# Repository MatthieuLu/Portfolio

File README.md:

# Portfolio
 
Hello, and welcome to my Portfolio!

My name is Matt, and I'm an Aerospace Engineering Student in the UCI Class of 2022.

I'm currently working towards getting my foot in the door to the Aerospace sector, hopefully as a Systems Engineer.

Here is a culmination of all of my past documented works, so feel free to browse and download what you would like.

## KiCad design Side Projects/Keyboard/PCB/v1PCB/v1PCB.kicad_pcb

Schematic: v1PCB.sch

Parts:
D_0, D_1, D_2, D_3, D_4, D_5, D_6, D_7, D_8, D_9, D_10, D_11, D_12, D_13, D_14, D_15, D_16, D_17, D_18, D_19, D_20, D_21, D_22, D_23, D_24, D_25, D_26, D_27, D_28, D_29, D_30, D_31, D_32, D_33, D_34, D_35, D_36, D_37, D_38, D_39, D_40, D_41, D_42, D_43, D_44, D_45, D_46, D_47, D_48, D_49, D_50, D_51, D_52, D_53, D_54, D_55, D_56, D_57, D_58, D_59, D_60, D_61, D_62, D_63, D_64, D_65, D_66, D_67, D_68, D_69, D_70, D_71, D_72, D_73, D_74, D_75, D_76, D_77, D_78, D_79, D_80, D_81, D_82, D_83, D_84, D_85, D_86, D_87, D_88, D_89, D_90, D_91, D_92, D_93, D_94, D_95, D_96, D_97, D_98, D_99, D_100: D; D_SOD-123
K_0, K_1, K_2, K_3, K_4, K_5, K_6, K_7, K_8, K_9, K_10, K_11, K_12, K_13, K_14, K_15, K_16, K_17, K_18, K_19, K_20, K_21, K_22, K_23, K_24, K_25, K_26, K_27, K_28, K_29, K_30, K_31, K_33, K_34, K_35, K_36, K_38, K_39, K_40, K_41, K_42, K_43, K_44, K_45, K_46, K_47, K_48, K_49, K_51, K_52, K_53, K_54, K_56, K_57, K_58, K_59, K_60, K_61, K_62, K_63, K_64, K_65, K_66, K_68, K_69, K_70, K_72, K_73, K_74, K_75, K_76, K_77, K_78, K_79, K_80, K_81, K_83, K_84, K_85, K_86, K_87, K_96, K_97, K_98, K_99, K_100: KEYSW; MX-1U-NoLED
K_32: KEYSW; MX-2U-NoLED
K_37, K_50: KEYSW; MX-1.5U-NoLED
K_55, K_82: KEYSW; MX-1.75U-NoLED
K_67, K_71, K_91: KEYSW; MX-2.25U-NoLED
K_88, K_89, K_90, K_92, K_94, K_95: KEYSW; MX-1.25U-NoLED
K_93: KEYSW; MX-2.75U-NoLED

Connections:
unnamed: D_0.2 (A), K_0.2
unnamed: D_1.2 (A), K_1.2
unnamed: D_2.2 (A), K_2.2
unnamed: D_3.2 (A), K_3.2
unnamed: D_4.2 (A), K_4.2
unnamed: D_5.2 (A), K_5.2
unnamed: D_6.2 (A), K_6.2
unnamed: D_7.2 (A), K_7.2
unnamed: D_8.2 (A), K_8.2
unnamed: D_9.2 (A), K_9.2
unnamed: D_10.2 (A), K_10.2
unnamed: D_11.2 (A), K_11.2
unnamed: D_12.2 (A), K_12.2
unnamed: D_13.2 (A), K_13.2
unnamed: D_14.2 (A), K_14.2
unnamed: D_15.2 (A), K_15.2
unnamed: D_16.2 (A), K_16.2
unnamed: D_17.2 (A), K_17.2
unnamed: D_18.2 (A), K_18.2
unnamed: D_19.2 (A), K_19.2
unnamed: D_20.2 (A), K_20.2
unnamed: D_21.2 (A), K_21.2
unnamed: D_22.2 (A), K_22.2
unnamed: D_23.2 (A), K_23.2
unnamed: D_24.2 (A), K_24.2
unnamed: D_25.2 (A), K_25.2
unnamed: D_26.2 (A), K_26.2
unnamed: D_27.2 (A), K_27.2
unnamed: D_28.2 (A), K_28.2
unnamed: D_29.2 (A), K_29.2
unnamed: D_30.2 (A), K_30.2
unnamed: D_31.2 (A), K_31.2
unnamed: D_32.2 (A), K_32.2
unnamed: D_33.2 (A), K_33.2
unnamed: D_34.2 (A), K_34.2
unnamed: D_35.2 (A), K_35.2
unnamed: D_36.2 (A), K_36.2
unnamed: D_37.2 (A), K_37.2
unnamed: D_38.2 (A), K_38.2
unnamed: D_39.2 (A), K_39.2
unnamed: D_40.2 (A), K_40.2
unnamed: D_41.2 (A), K_41.2
unnamed: D_42.2 (A), K_42.2
unnamed: D_43.2 (A), K_43.2
unnamed: D_44.2 (A), K_44.2
unnamed: D_45.2 (A), K_45.2
unnamed: D_46.2 (A), K_46.2
unnamed: D_47.2 (A), K_47.2
unnamed: D_48.2 (A), K_48.2
unnamed: D_49.2 (A), K_49.2
unnamed: D_50.2 (A), K_50.2
unnamed: D_51.2 (A), K_51.2
unnamed: D_52.2 (A), K_52.2
unnamed: D_53.2 (A), K_53.2
unnamed: D_54.2 (A), K_54.2
unnamed: D_55.2 (A), K_55.2
unnamed: D_56.2 (A), K_56.2
unnamed: D_57.2 (A), K_57.2
unnamed: D_58.2 (A), K_58.2
unnamed: D_59.2 (A), K_59.2
unnamed: D_60.2 (A), K_60.2
unnamed: D_61.2 (A), K_61.2
unnamed: D_62.2 (A), K_62.2
unnamed: D_63.2 (A), K_63.2
unnamed: D_64.2 (A), K_64.2
unnamed: D_65.2 (A), K_65.2
unnamed: D_66.2 (A), K_66.2
unnamed: D_67.2 (A), K_67.2
unnamed: D_68.2 (A), K_68.2
unnamed: D_69.2 (A), K_69.2
unnamed: D_70.2 (A), K_70.2
unnamed: D_71.2 (A), K_71.2
unnamed: D_72.2 (A), K_72.2
unnamed: D_73.2 (A), K_73.2
unnamed: D_74.2 (A), K_74.2
unnamed: D_75.2 (A), K_75.2
unnamed: D_76.2 (A), K_76.2
unnamed: D_77.2 (A), K_77.2
unnamed: D_78.2 (A), K_78.2
unnamed: D_79.2 (A), K_79.2
unnamed: D_80.2 (A), K_80.2
unnamed: D_81.2 (A), K_81.2
unnamed: D_82.2 (A), K_82.2
unnamed: D_83.2 (A), K_83.2
unnamed: D_84.2 (A), K_84.2
unnamed: D_85.2 (A), K_85.2
unnamed: D_86.2 (A), K_86.2
unnamed: D_87.2 (A), K_87.2
unnamed: D_88.2 (A), K_88.2
unnamed: D_89.2 (A), K_89.2
unnamed: D_90.2 (A), K_90.2
unnamed: D_91.2 (A), K_91.2
unnamed: D_92.2 (A), K_92.2
unnamed: D_93.2 (A), K_93.2
unnamed: D_94.2 (A), K_94.2
unnamed: D_95.2 (A), K_95.2
unnamed: D_96.2 (A), K_96.2
unnamed: D_97.2 (A), K_97.2
unnamed: D_98.2 (A), K_98.2
unnamed: D_99.2 (A), K_99.2
unnamed: D_100.2 (A), K_100.2
col0: K_0.1, K_19.1, K_37.1, K_55.1, K_88.1
col1: K_1.1, K_20.1, K_71.1, K_89.1
col2: K_2.1, K_21.1, K_38.1, K_56.1, K_72.1
col3: K_3.1, K_22.1, K_39.1, K_57.1, K_73.1, K_90.1
col4: K_4.1, K_23.1, K_40.1, K_58.1, K_74.1, K_91.1
col5: K_5.1, K_24.1, K_41.1, K_59.1, K_75.1
col6: K_6.1, K_25.1, K_42.1, K_60.1, K_76.1, K_92.1
col7: K_7.1, K_26.1, K_43.1, K_61.1, K_77.1
col8: K_8.1, K_27.1, K_44.1, K_62.1, K_78.1, K_93.1
col9: K_9.1, K_28.1, K_45.1, K_63.1, K_79.1
col10: K_10.1, K_29.1, K_46.1, K_64.1, K_80.1, K_94.1
col11: K_11.1, K_30.1, K_47.1, K_65.1, K_81.1, K_95.1
col12: K_12.1, K_31.1, K_48.1, K_66.1
col13: K_13.1, K_49.1, K_67.1, K_82.1, K_96.1
col14: K_14.1, K_32.1, K_50.1, K_83.1, K_97.1
col15: K_15.1, K_33.1, K_51.1, K_68.1, K_84.1, K_98.1
col16: K_16.1, K_34.1, K_52.1, K_69.1, K_85.1, K_99.1
col17: K_17.1, K_35.1, K_53.1, K_70.1, K_86.1, K_100.1
col18: K_18.1, K_36.1, K_54.1, K_87.1
row0: D_0.1 (K), D_1.1 (K), D_2.1 (K), D_3.1 (K), D_4.1 (K), D_5.1 (K), D_6.1 (K), D_7.1 (K), D_8.1 (K), D_9.1 (K), D_10.1 (K), D_11.1 (K), D_12.1 (K), D_13.1 (K), D_14.1 (K), D_15.1 (K), D_16.1 (K), D_17.1 (K), D_18.1 (K)
row1: D_19.1 (K), D_20.1 (K), D_21.1 (K), D_22.1 (K), D_23.1 (K), D_24.1 (K), D_25.1 (K), D_26.1 (K), D_27.1 (K), D_28.1 (K), D_29.1 (K), D_30.1 (K), D_31.1 (K), D_32.1 (K), D_33.1 (K), D_34.1 (K), D_35.1 (K), D_36.1 (K)
row2: D_37.1 (K), D_38.1 (K), D_39.1 (K), D_40.1 (K), D_41.1 (K), D_42.1 (K), D_43.1 (K), D_44.1 (K), D_45.1 (K), D_46.1 (K), D_47.1 (K), D_48.1 (K), D_49.1 (K), D_50.1 (K), D_51.1 (K), D_52.1 (K), D_53.1 (K)
row3: D_54.1 (K), D_55.1 (K), D_56.1 (K), D_57.1 (K), D_58.1 (K), D_59.1 (K), D_60.1 (K), D_61.1 (K), D_62.1 (K), D_63.1 (K), D_64.1 (K), D_65.1 (K), D_66.1 (K), D_67.1 (K), D_68.1 (K), D_69.1 (K), D_70.1 (K)
row4: D_71.1 (K), D_72.1 (K), D_73.1 (K), D_74.1 (K), D_75.1 (K), D_76.1 (K), D_77.1 (K), D_78.1 (K), D_79.1 (K), D_80.1 (K), D_81.1 (K), D_82.1 (K), D_83.1 (K), D_84.1 (K), D_85.1 (K), D_86.1 (K)
row5: D_87.1 (K), D_88.1 (K), D_89.1 (K), D_90.1 (K), D_91.1 (K), D_92.1 (K), D_93.1 (K), D_94.1 (K), D_95.1 (K), D_96.1 (K), D_97.1 (K), D_98.1 (K), D_99.1 (K), D_100.1 (K)

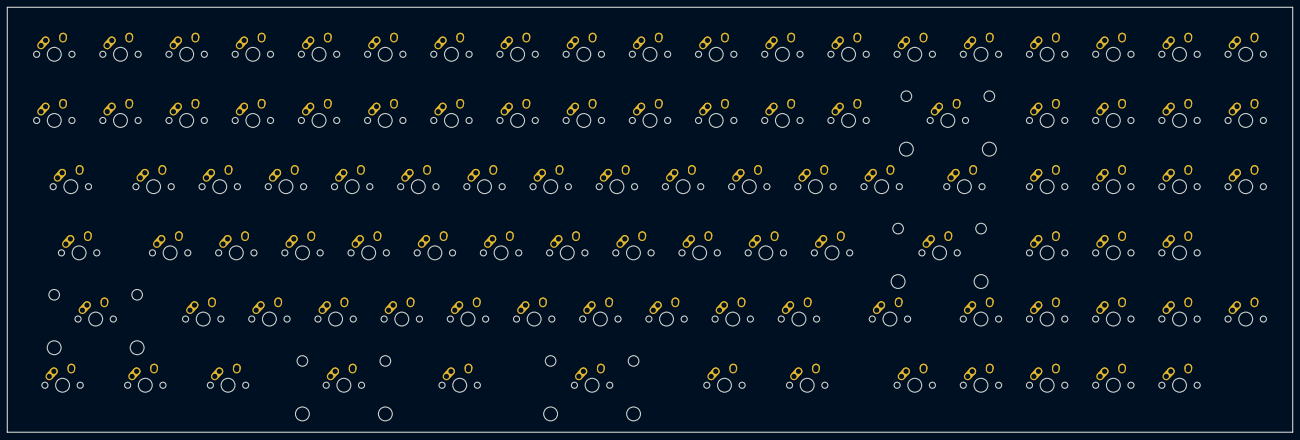
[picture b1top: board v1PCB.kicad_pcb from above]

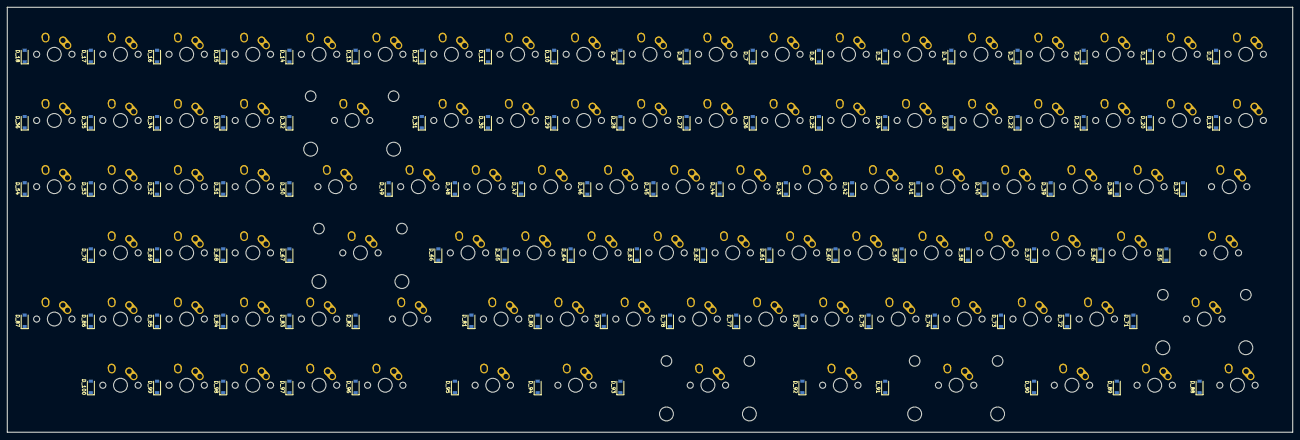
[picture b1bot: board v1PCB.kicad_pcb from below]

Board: 2 copper layers, 369.9 x 122.3 mm, 202 parts (101 on the bottom side), 126 nets, no tracks yet.

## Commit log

2021-10-03 Side Projects added
2021-12-28 Update to Portfolio
2021-12-28 Update to README
2021-12-28 Addition of project
2022-07-19 Addition of Senior Project
    Added all files related to transport aircraft design
2022-07-19 Updated Portfolio file names
    Moved some files around and updated file names to make organization more clear
